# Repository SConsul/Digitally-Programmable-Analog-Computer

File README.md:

# Digitally-Programmable-Analog-Computer

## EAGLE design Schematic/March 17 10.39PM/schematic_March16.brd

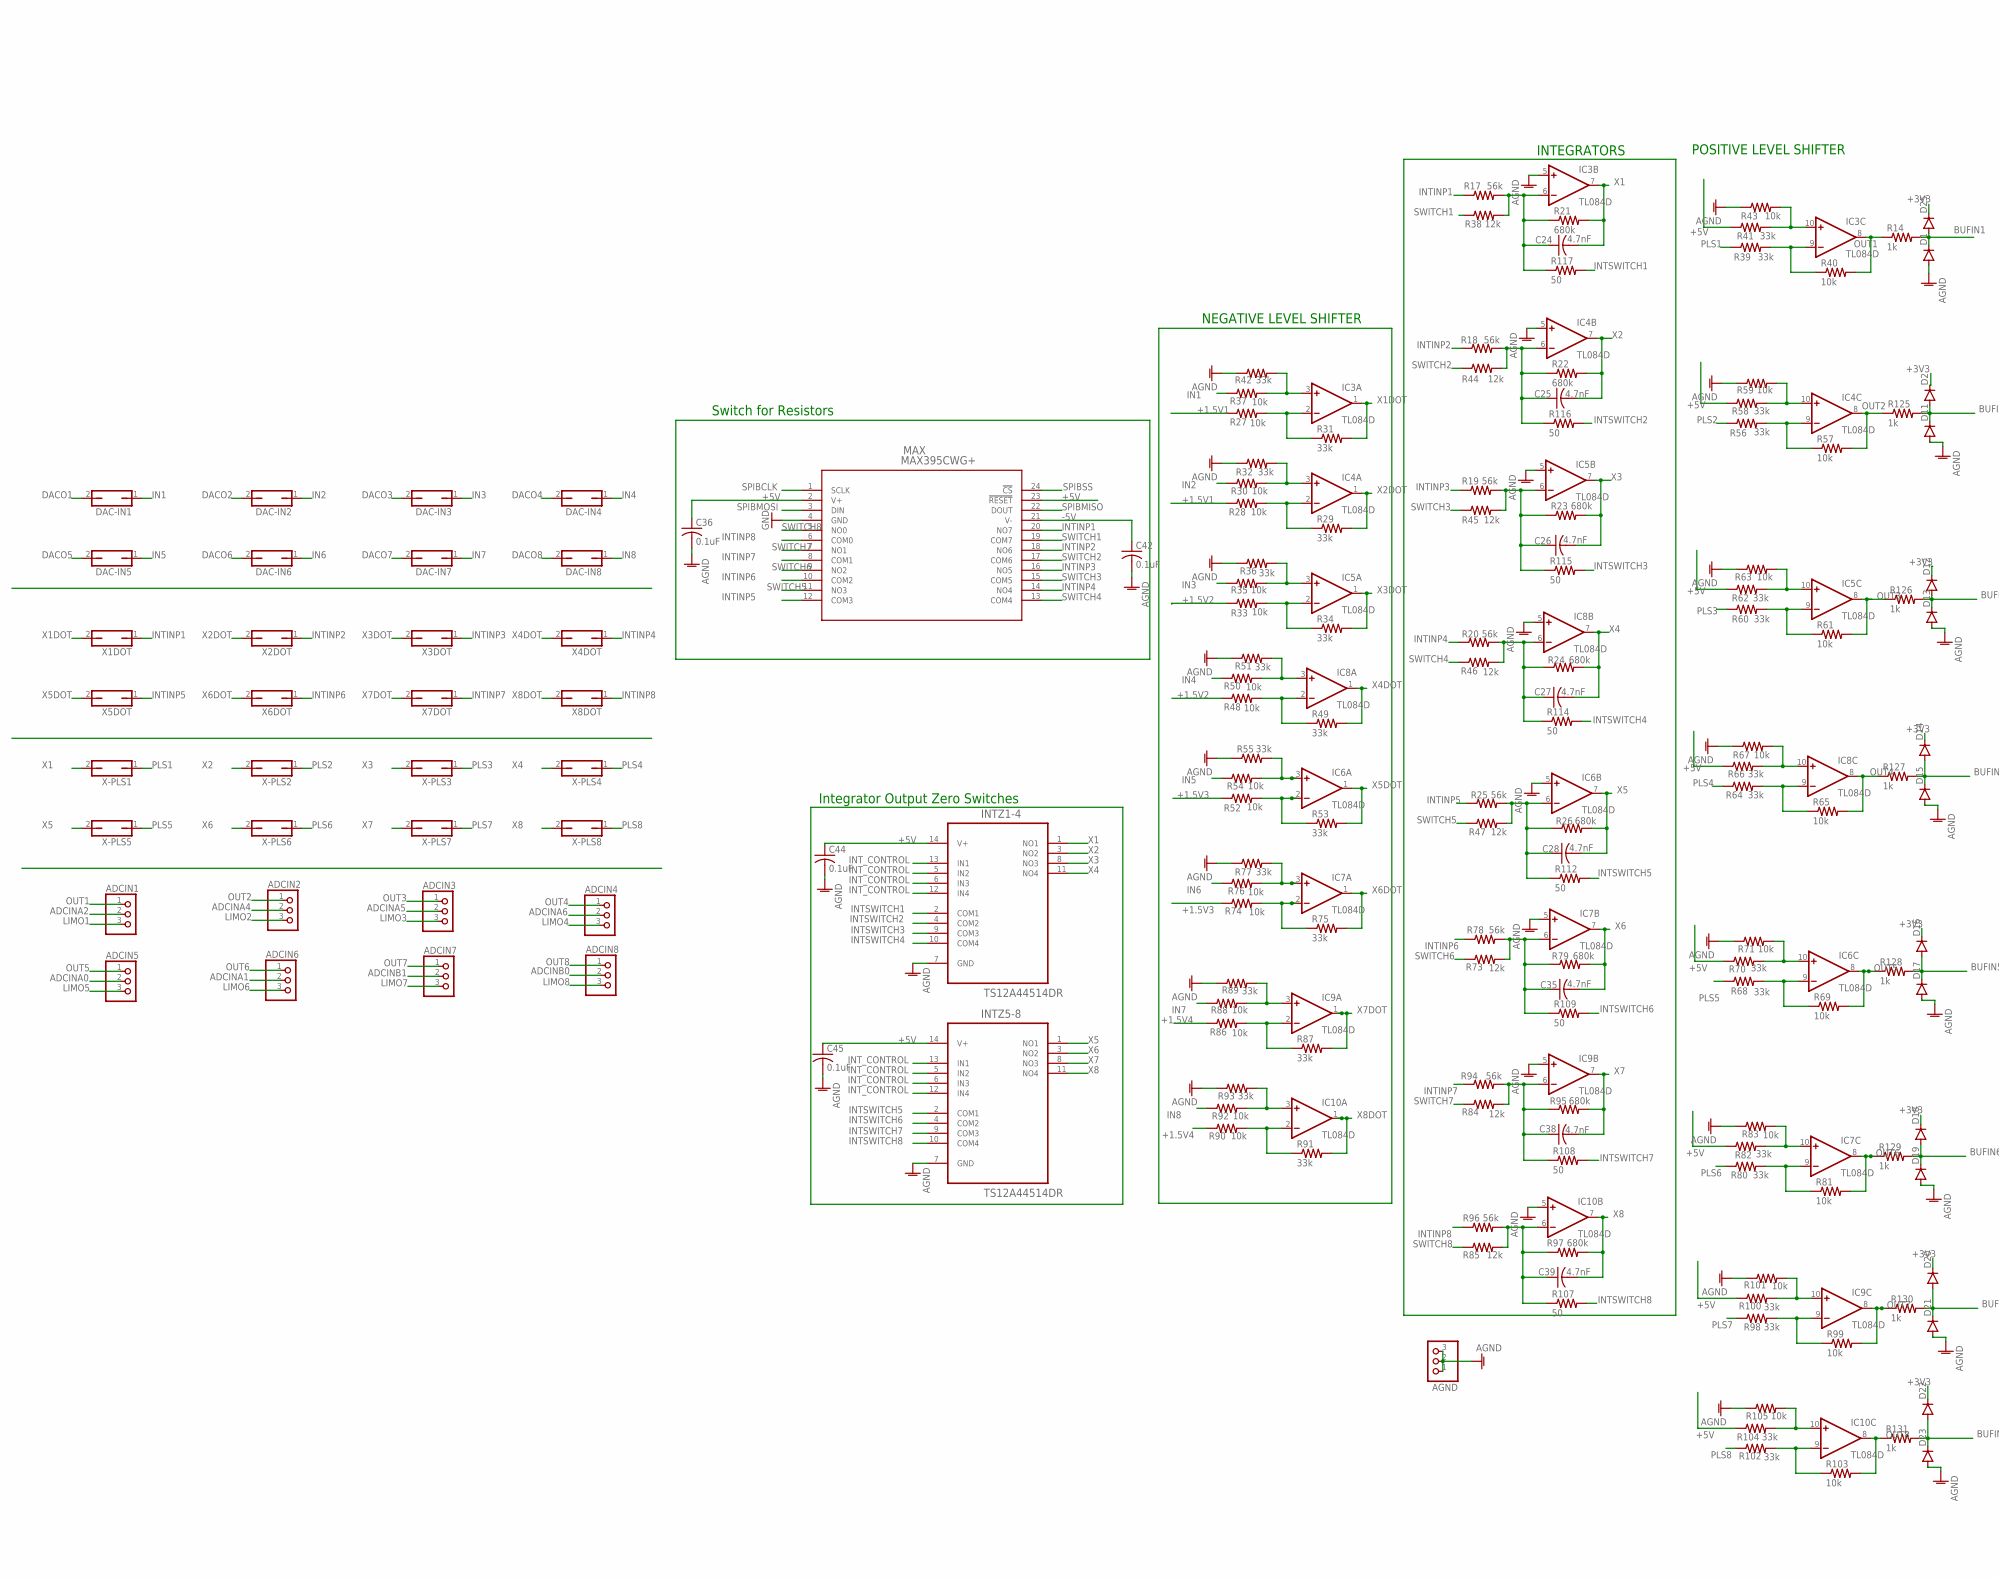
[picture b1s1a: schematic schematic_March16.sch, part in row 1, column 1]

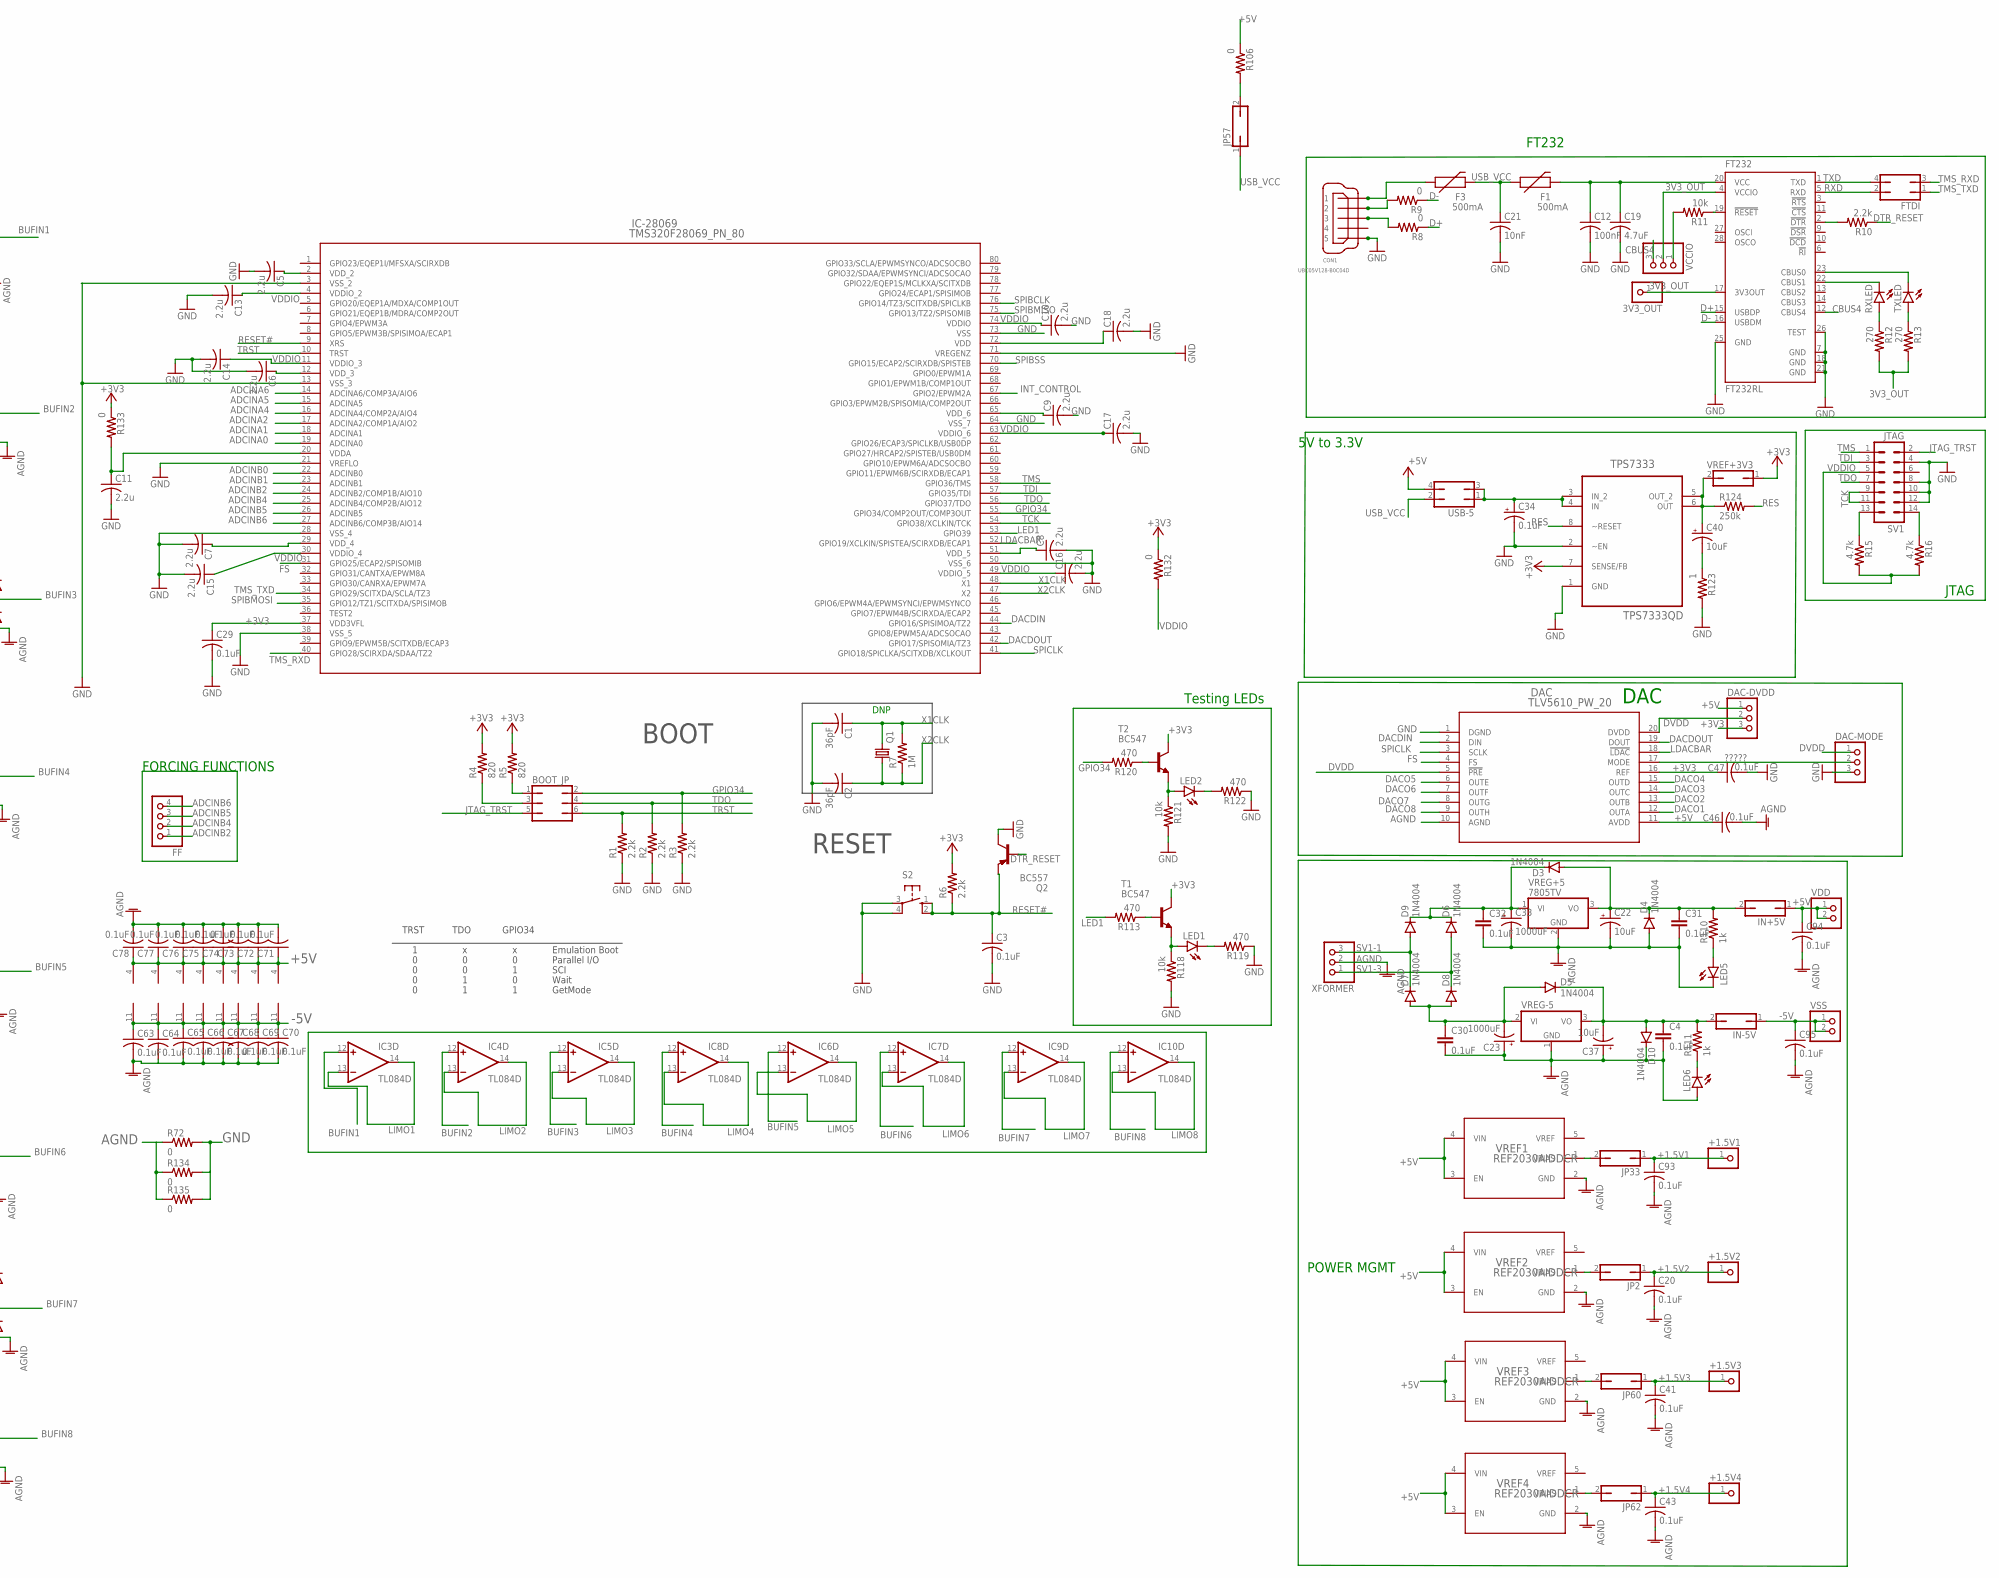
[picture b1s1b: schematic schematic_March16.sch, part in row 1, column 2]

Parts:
3V3_OUT: PINHD-1X1; 1X01
+1.5V1, +1.5V2, +1.5V3, +1.5V4: PINHD-1X1; 1X01
ADCIN1, ADCIN2, ADCIN3, ADCIN4, ADCIN5, ADCIN6, ADCIN7, ADCIN8: PINHD-1X3; 1X03
AGND: PINHD-1X3; 1X03
BOOT_JP: JP3Q
C1, C2: 36pF; C1206
C3, C4, C20, C29, C30, C31, C32, C36, C41, C42, C43, C44, C45, C46, C47, C63, C64, C65, C66, C67, C68, C69, C70, C71, C72, C73, C74, C75, C76, C77, C78, C93, C94, C95: 0.1uF; C1206
C5, C6, C7, C8, C9, C10, C11, C13, C14, C15, C16, C17, C18: 2.2u; C1206
C12: 100nF; C1206
C19: 4.7uF; C1206
C21: 10nF; C1206
C22, C37, C40: 10uF; E2,5-7
C23, C33: 1000uF; E2,5-7
C24, C25, C26, C27, C28, C35, C38, C39: 4.7nF; C1206
C34: 0.1uF; E2,5-7
CON1: UBC05V128-B0C04D; 32005-201
D1, D2, D11, D12, D13, D14, D15, D16, D17, D18, D19, D20, D21, D22, D23, D25: DIODE-DO214AA; DO214AA
D3, D4, D5, D6, D7, D8, D9, D10: 1N4004; DO41-10
DAC: TLV5610_PW_20; PW20
DAC-DVDD: PINHD-1X3; 1X03
DAC-IN1, DAC-IN2, DAC-IN3, DAC-IN4, DAC-IN5, DAC-IN6, DAC-IN7, DAC-IN8: JP1Q; JP1
DAC-MODE: PINHD-1X3; 1X03
F1, F3: 500mA; 0603
FF: PINHD-1X4; 1X04
FT232: FT232RL; SSOP28
FTDI: JP2Q
IC3, IC4, IC5, IC6, IC7, IC8, IC9, IC10: TL084D; SO14
IC-28069: TMS320F28069_PN_80; PN80
IN+5V: JP1Q; JP1
IN-5V: JP1Q; JP1
INTZ1-4, INTZ5-8: TS12A44514DR; SOIC127P600X175-14N
JP2, JP33, JP57, JP60, JP62: JP1Q; JP1
LED1, LED2, LED5, LED6: LEDSML1206; SML1206
MAX: MAX395CWG+; 21-0042B_24
Q1: CRYSTALHC49S; HC49/S
Q2: BC557; TO92-EBC
R1, R2, R3, R6, R10: 2.2k; R1206
R4, R5: 820; R1206
R7: 1M; R1206
R8, R9, R72, R106, R132, R133, R134, R135: 0; R1206
R11, R27, R28, R30, R33, R35, R37, R40, R43, R48, R50, R52, R54, R57, R59, R61, R63, R65, R67, R69, R71, R74, R76, R81, R83, R86, R88, R90, R92, R99, R101, R103, R105, R118, R121: 10k; R1206
R12, R13: 270; R1206
R14, R125, R126, R127, R128, R129, R130, R131: 1k; R1206
R15, R16: 4.7k; M1206
R17, R18, R19, R20, R25, R78, R94, R96: 56k; R1206
R21, R22, R23, R24, R26, R79, R95, R97: 680k; R1206
R29, R31, R32, R34, R36, R39, R41, R42, R49, R51, R53, R55, R56, R58, R60, R62, R64, R66, R68, R70, R75, R77, R80, R82, R87, R89, R91, R93, R98, R100, R102, R104: 33k; R1206
R38, R44, R45, R46, R47, R73, R84, R85: 12k; R1206
R107, R108, R109, R112, R114, R115, R116, R117: 50; R1206
R110, R111: 1k; 0207/10
R113, R119, R120, R122: 470; R1206
R123: 1; M1206
R124: 250k; M1206
RXLED: LEDSML1206; SML1206
S2: 10-XX; B3F-10XX
SV1: JTAG; MA07-2
T1, T2: BC547; TO92
TPS7333: TPS7333QD; SOIC127P600X175-8N
TXLED: LEDSML1206; SML1206
USB-5: JP2Q
VCCIO: PINHD-1X3; 1X03
VDD: PINHD-1X2; 1X02
VREF1, VREF2, VREF3, VREF4: REF2030AIDDCR; DDC0005A_N
VREF+3V3: JP1Q; JP1
VREG+5: 7805TV; TO220V
VREG-5: 7905T; TO220H
VSS: PINHD-1X2; 1X02
X1DOT, X2DOT, X3DOT, X4DOT, X5DOT, X6DOT, X7DOT, X8DOT: JP1Q; JP1
X-PLS1, X-PLS2, X-PLS3, X-PLS4, X-PLS5, X-PLS6, X-PLS7, X-PLS8: JP1Q; JP1
XFORMER: PINHD-1X3; 1X03

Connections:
3V3_OUT: 3V3_OUT.1, FT232.4 (VCCIO), FT232.17 (3V3OUT), R12.2, R13.2, VCCIO.2
+1.5V1: +1.5V1.1, C93.1, JP33.1, R27.1, R28.1
+1.5V2: +1.5V2.1, C20.1, JP2.1, R33.1, R48.1
+1.5V3: +1.5V3.1, C41.1, JP60.1, R52.1, R74.1
+1.5V4: +1.5V4.1, C43.1, JP62.1, R86.1, R90.1
+3V3: C29.1, C47.1, D2.C, D12.C, D14.C, D16.C, D18.C, D20.C, D22.C, D25.C, DAC.16 (REF), DAC-DVDD.3, IC-28069.37 (VDD3VFL), R4.2, R5.2, R6.2, R132.1, R133.1, T1.3 (C), T2.3 (C), TPS7333.7 (SENSE/FB), VREF+3V3.1
+5V: C36.1, C44.1, C45.1, C46.1, C71.1, C72.1, C73.1, C74.1, C75.1, C76.1, C77.1, C78.1, C94.1, DAC.11 (AVDD), DAC-DVDD.1, IC3.4 (V+), IC4.4 (V+), IC5.4 (V+), IC6.4 (V+), IC7.4 (V+), IC8.4 (V+), IC9.4 (V+), IC10.4 (V+), IN+5V.1, INTZ1-4.14 (V+), INTZ5-8.14 (V+), MAX.2 (V+), MAX.23 (!RESET), R41.1, R58.1, R62.1, R66.1, R70.1, R82.1, R100.1, R104.1, R106.1, USB-5.4, VDD.1, VDD.2, VREF1.3 (EN), VREF1.4 (VIN), VREF2.3 (EN), VREF2.4 (VIN), VREF3.3 (EN), VREF3.4 (VIN), VREF4.3 (EN), VREF4.4 (VIN)
-5V: C42.1, C63.1, C64.1, C65.1, C66.1, C67.1, C68.1, C69.1, C70.1, C95.1, IC3.11 (V-), IC4.11 (V-), IC5.11 (V-), IC6.11 (V-), IC7.11 (V-), IC8.11 (V-), IC9.11 (V-), IC10.11 (V-), IN-5V.1, MAX.21 (V-), VSS.1, VSS.2
?????: DAC.17 (MODE), DAC-MODE.2
ADCINA0: ADCIN5.2, IC-28069.19 (ADCINA0)
ADCINA1: ADCIN6.2, IC-28069.18 (ADCINA1)
ADCINA2: ADCIN1.2, IC-28069.17 (ADCINA2/COMP1A/AIO2)
ADCINA4: ADCIN2.2, IC-28069.16 (ADCINA4/COMP2A/AIO4)
ADCINA5: ADCIN3.2, IC-28069.15 (ADCINA5)
ADCINA6: ADCIN4.2, IC-28069.14 (ADCINA6/COMP3A/AIO6)
ADCINB0: ADCIN8.2, IC-28069.22 (ADCINB0)
ADCINB1: ADCIN7.2, IC-28069.23 (ADCINB1)
ADCINB2: FF.1, IC-28069.24 (ADCINB2/COMP1B/AIO10)
ADCINB4: FF.2, IC-28069.25 (ADCINB4/COMP2B/AIO12)
ADCINB5: FF.3, IC-28069.26 (ADCINB5)
ADCINB6: FF.4, IC-28069.27 (ADCINB6/COMP3B/AIO14)
AGND: AGND.1, AGND.2, AGND.3, C4.2, C20.2, C22.-, C23.+, C30.2, C31.2, C32.2, C33.-, C36.2, C37.+, C41.2, C42.2, C43.2, C44.2, C45.2, C46.2, C63.2, C64.2, C65.2, C66.2, C67.2, C68.2, C69.2, C70.2, C71.2, C72.2, C73.2, C74.2, C75.2, C76.2, C77.2, C78.2, C93.2, C94.2, C95.2, D1.A, D4.A, D10.C, D11.A, D13.A, D15.A, D17.A, D19.A, D21.A, D23.A, DAC.10 (AGND), IC3.5 (+IN), IC4.5 (+IN), IC5.5 (+IN), IC6.5 (+IN), IC7.5 (+IN), IC8.5 (+IN), IC9.5 (+IN), IC10.5 (+IN), INTZ1-4.7 (GND), INTZ5-8.7 (GND), LED5.C, LED6.A, R32.1, R36.1, R42.1, R43.1, R51.1, R55.1, R59.1, R63.1, R67.1, R71.1, R72.1, R77.1, R83.1, R89.1, R93.1, R101.1, R105.1, R134.1, R135.1, VREF1.2 (GND), VREF2.2 (GND), VREF3.2 (GND), VREF4.2 (GND), VREG+5.2 (GND), VREG-5.1 (GND), XFORMER.2
BUFIN1: D1.C, D25.A, IC3.12 (+IN), R14.2
BUFIN2: D2.A, D11.C, IC4.12 (+IN), R125.2
BUFIN3: D12.A, D13.C, IC5.12 (+IN), R126.2
BUFIN4: D14.A, D15.C, IC8.12 (+IN), R127.2
BUFIN5: D16.A, D17.C, IC6.12 (+IN), R128.2
BUFIN6: D18.A, D19.C, IC7.12 (+IN), R129.2
BUFIN7: D20.A, D21.C, IC9.12 (+IN), R130.2
BUFIN8: D22.A, D23.C, IC10.12 (+IN), R131.2
CBUS4: FT232.12 (CBUS4), VCCIO.3
D+: FT232.15 (USBDP), R8.1
D-: FT232.16 (USBDM), R9.1
DACDIN: DAC.2 (DIN), IC-28069.44 (GPIO16/SPISIMOA/TZ2)
DACDOUT: DAC.19 (DOUT), IC-28069.42 (GPIO17/SPISOMIA/TZ3)
DACO1: DAC.12 (OUTA), DAC-IN1.2
DACO2: DAC.13 (OUTB), DAC-IN2.2
DACO3: DAC.14 (OUTC), DAC-IN3.2
DACO4: DAC.15 (OUTD), DAC-IN4.2
DACO5: DAC.6 (OUTE), DAC-IN5.2
DACO6: DAC.7 (OUTF), DAC-IN6.2
DACO7: DAC.8 (OUTG), DAC-IN7.2
DACO8: DAC.9 (OUTH), DAC-IN8.2
DTR_RESET: Q2.B, R10.1
DVDD: DAC.5 (!PRE), DAC.20 (DVDD), DAC-DVDD.2, DAC-MODE.1
FS: DAC.4 (FS), IC-28069.31 (GPIO25/ECAP2/SPISOMIB)
GND: C1.2, C2.2, C3.2, C5.2, C6.2, C7.2, C8.2, C9.2, C10.2, C11.2, C12.2, C13.2, C14.2, C15.2, C16.2, C17.2, C18.2, C19.2, C21.2, C29.2, C34.-, C47.2, CON1.5, DAC.1 (DGND), DAC-MODE.3, FT232.7 (GND), FT232.18 (GND), FT232.21 (GND), FT232.25 (GND), FT232.26 (TEST), IC-28069.3 (VSS_2), IC-28069.13 (VSS_3), IC-28069.21 (VREFLO), IC-28069.28 (VSS_4), IC-28069.38 (VSS_5), IC-28069.50 (VSS_6), IC-28069.64 (VSS_7), IC-28069.71 (VREGENZ), IC-28069.73 (VSS), MAX.4 (GND), Q2.C, R1.1, R2.1, R3.1, R72.2, R118.2, R119.1, R121.2, R122.1, R123.2, R134.2, R135.2, S2.3, S2.4 (P1), SV1.4, SV1.8, SV1.10, SV1.12, TPS7333.1 (GND), TPS7333.2 (~EN)
GPIO34: BOOT_JP.2, IC-28069.55 (GPIO34/COMP2OUT/COMP3OUT), R3.2, R120.2
IDK: C22.+, C31.1, D3.A, D4.C, IN+5V.2, R110.2, VREG+5.3 (VO)
IDK2: C4.1, C37.-, D5.C, D10.A, IN-5V.2, R111.2, VREG-5.3 (VO)
IN1: DAC-IN1.1, R37.1
IN2: DAC-IN2.1, R30.1
IN3: DAC-IN3.1, R35.1
IN4: DAC-IN4.1, R50.1
IN5: DAC-IN5.1, R54.1
IN6: DAC-IN6.1, R76.1
IN7: DAC-IN7.1, R88.1
IN8: DAC-IN8.1, R92.1
INTINP1: MAX.20 (NO7), R17.1, X1DOT.1
INTINP2: MAX.18 (NO6), R18.1, X2DOT.1
INTINP3: MAX.16 (NO5), R19.1, X3DOT.1
INTINP4: MAX.14 (NO4), R20.1, X4DOT.1
INTINP5: MAX.12 (COM3), R25.1, X5DOT.1
INTINP6: MAX.10 (COM2), R78.1, X6DOT.1
INTINP7: MAX.8 (COM1), R94.1, X7DOT.1
INTINP8: MAX.6 (COM0), R96.1, X8DOT.1
INTSWITCH1: INTZ1-4.2 (COM1), R117.2
INTSWITCH2: INTZ1-4.4 (COM2), R116.2
INTSWITCH3: INTZ1-4.9 (COM3), R115.2
INTSWITCH4: INTZ1-4.10 (COM4), R114.2
INTSWITCH5: INTZ5-8.2 (COM1), R112.2
INTSWITCH6: INTZ5-8.4 (COM2), R109.2
INTSWITCH7: INTZ5-8.9 (COM3), R108.2
INTSWITCH8: INTZ5-8.10 (COM4), R107.2
INT_CONTROL: IC-28069.67 (GPIO2/EPWM2A), INTZ1-4.5 (IN2), INTZ1-4.6 (IN3), INTZ1-4.12 (IN4), INTZ1-4.13 (IN1), INTZ5-8.5 (IN2), INTZ5-8.6 (IN3), INTZ5-8.12 (IN4), INTZ5-8.13 (IN1)
JTAG_TRST: BOOT_JP.5, SV1.2
LDACBAR: DAC.18 (!LDAC), IC-28069.52 (GPIO19/XCLKIN/SPISTEA/SCIRXDB/ECAP1)
LED1: IC-28069.53 (GPIO39), R113.2
LIMO1: ADCIN1.3, IC3.13 (-IN), IC3.14 (OUT)
LIMO2: ADCIN2.3, IC4.13 (-IN), IC4.14 (OUT)
LIMO3: ADCIN3.3, IC5.13 (-IN), IC5.14 (OUT)
LIMO4: ADCIN4.3, IC8.13 (-IN), IC8.14 (OUT)
LIMO5: ADCIN5.3, IC6.13 (-IN), IC6.14 (OUT)
LIMO6: ADCIN6.3, IC7.13 (-IN), IC7.14 (OUT)
LIMO7: ADCIN7.3, IC9.13 (-IN), IC9.14 (OUT)
LIMO8: ADCIN8.3, IC10.13 (-IN), IC10.14 (OUT)
unnamed: C5.1, IC-28069.2 (VDD_2)
unnamed: C6.1, IC-28069.12 (VDD_3)
unnamed: C7.1, IC-28069.29 (VDD_4)
unnamed: C8.1, IC-28069.51 (VDD_5)
unnamed: C9.1, IC-28069.65 (VDD_6)
unnamed: FT232.2 (!DTR), R10.2
unnamed: C11.1, IC-28069.20 (VDDA), R133.2
unnamed: C18.1, IC-28069.72 (VDD)
unnamed: BOOT_JP.1, R5.1
unnamed: BOOT_JP.3, R4.1
unnamed: CON1.2, R9.2
unnamed: CON1.3, R8.2
unnamed: FT232.19 (!RESET), R11.1
unnamed: FT232.22 (CBUS1), RXLED.C
unnamed: FT232.23 (CBUS0), TXLED.C
unnamed: R12.1, RXLED.A
unnamed: R13.1, TXLED.A
unnamed: C25.1, IC4.6 (-IN), R18.2, R22.1, R44.2, R116.1
unnamed: C26.1, IC5.6 (-IN), R19.2, R23.1, R45.2, R115.1
unnamed: C27.1, IC8.6 (-IN), R20.2, R24.1, R46.2, R114.1
unnamed: IC4.2 (-IN), R28.2, R29.1
unnamed: R15.1, SV1.13
unnamed: R16.1, SV1.14
unnamed: IC4.3 (+IN), R30.2, R32.2
unnamed: C24.1, IC3.6 (-IN), R17.2, R21.1, R38.2, R117.1
unnamed: IC3.2 (-IN), R27.2, R31.1
unnamed: C28.1, IC6.6 (-IN), R25.2, R26.1, R47.2, R112.1
unnamed: IC5.2 (-IN), R33.2, R34.1
unnamed: IC3.3 (+IN), R37.2, R42.2
unnamed: IC5.3 (+IN), R35.2, R36.2
unnamed: IC3.9 (-IN), R39.2, R40.1
unnamed: IC3.10 (+IN), R41.2, R43.2
unnamed: IC8.2 (-IN), R48.2, R49.1
unnamed: IC8.3 (+IN), R50.2, R51.2
unnamed: IC7.2 (-IN), R74.2, R75.1
unnamed: IC6.2 (-IN), R52.2, R53.1
unnamed: IC6.3 (+IN), R54.2, R55.2
unnamed: IC7.3 (+IN), R76.2, R77.2
unnamed: IC4.9 (-IN), R56.2, R57.1
unnamed: IC4.10 (+IN), R58.2, R59.2
unnamed: IC5.9 (-IN), R60.2, R61.1
unnamed: IC5.10 (+IN), R62.2, R63.2
unnamed: IC8.9 (-IN), R64.2, R65.1
unnamed: IC8.10 (+IN), R66.2, R67.2
unnamed: IC6.9 (-IN), R68.2, R69.1
unnamed: IC6.10 (+IN), R70.2, R71.2
unnamed: C35.1, IC7.6 (-IN), R73.2, R78.2, R79.1, R109.1
unnamed: IC7.9 (-IN), R80.2, R81.1
unnamed: IC7.10 (+IN), R82.2, R83.2
unnamed: IC9.2 (-IN), R86.2, R87.1
unnamed: IC9.3 (+IN), R88.2, R89.2
unnamed: IC10.2 (-IN), R90.2, R91.1
unnamed: IC10.3 (+IN), R92.2, R93.2
unnamed: C38.1, IC9.6 (-IN), R84.2, R94.2, R95.1, R108.1
unnamed: C39.1, IC10.6 (-IN), R85.2, R96.2, R97.1, R107.1
unnamed: IC9.9 (-IN), R98.2, R99.1
unnamed: IC9.10 (+IN), R100.2, R101.2
unnamed: IC10.9 (-IN), R102.2, R103.1
unnamed: IC10.10 (+IN), R104.2, R105.2
unnamed: C32.1, C33.+, D3.C, D6.C, D9.C, VREG+5.1 (VI)
unnamed: C40.+, R124.1, TPS7333.5 (OUT_2), TPS7333.6 (OUT), VREF+3V3.2
unnamed: C40.-, R123.1
unnamed: LED6.C, R111.1
unnamed: C34.+, TPS7333.3 (IN_2), TPS7333.4 (IN), USB-5.1, USB-5.3
unnamed: LED5.A, R110.1
unnamed: CON1.1, F3.1
unnamed: C23.-, C30.1, D5.A, D7.A, D8.A, VREG-5.2 (VI)
unnamed: JP33.2, VREF1.1 (VBIAS)
unnamed: R11.2, VCCIO.1
unnamed: R113.1, T1.2 (B)
unnamed: LED1.A, R118.1, T1.1 (E)
unnamed: LED1.C, R119.2
unnamed: R120.1, T2.2 (B)
unnamed: LED2.A, R121.1, T2.1 (E)
unnamed: LED2.C, R122.2
unnamed: JP2.2, VREF2.1 (VBIAS)
unnamed: JP57.2, R106.2
unnamed: JP60.2, VREF3.1 (VBIAS)
unnamed: JP62.2, VREF4.1 (VBIAS)
OUT1: ADCIN1.1, IC3.8 (OUT), R14.1, R40.2
OUT2: ADCIN2.1, IC4.8 (OUT), R57.2, R125.1
OUT3: ADCIN3.1, IC5.8 (OUT), R61.2, R126.1
OUT4: ADCIN4.1, IC8.8 (OUT), R65.2, R127.1
OUT5: ADCIN5.1, IC6.8 (OUT), R69.2, R128.1
OUT6: ADCIN6.1, IC7.8 (OUT), R81.2, R129.1
OUT7: ADCIN7.1, IC9.8 (OUT), R99.2, R130.1
OUT8: ADCIN8.1, IC10.8 (OUT), R103.2, R131.1
PLS1: R39.1, X-PLS1.1
PLS2: R56.1, X-PLS2.1
PLS3: R60.1, X-PLS3.1
PLS4: R64.1, X-PLS4.1
PLS5: R68.1, X-PLS5.1
PLS6: R80.1, X-PLS6.1
PLS7: R98.1, X-PLS7.1
PLS8: R102.1, X-PLS8.1
RES: R124.2, TPS7333.8 (~RESET)
RESET#: C3.1, IC-28069.9 (XRS), Q2.E, R6.1, S2.1 (S), S2.2 (S1)
RXD: FT232.5 (RXD), FTDI.2
SPIBCLK: IC-28069.76 (GPIO14/TZ3/SCITXDB/SPICLKB), MAX.1 (SCLK)
SPIBMISO: IC-28069.75 (GPIO13/TZ2/SPISOMIB), MAX.22 (DOUT)
SPIBMOSI: IC-28069.35 (GPIO12/TZ1/SCITXDA/SPISIMOB), MAX.3 (DIN)
SPIBSS: IC-28069.70 (GPIO15/ECAP2/SCIRXDB/SPISTEB), MAX.24 (!CS)
SPICLK: DAC.3 (SCLK), IC-28069.41 (GPIO18/SPICLKA/SCITXDB/XCLKOUT)
SV1-1: D7.C, D9.A, XFORMER.3
SV1-3: D6.A, D8.C, XFORMER.1
SWITCH1: MAX.19 (COM7), R38.1
SWITCH2: MAX.17 (COM6), R44.1
SWITCH3: MAX.15 (COM5), R45.1
SWITCH4: MAX.13 (COM4), R46.1
SWITCH5: MAX.11 (NO3), R47.1
SWITCH6: MAX.9 (NO2), R73.1
SWITCH7: MAX.7 (NO1), R84.1
SWITCH8: MAX.5 (NO0), R85.1
TCK: IC-28069.54 (GPIO38/XCLKIN/TCK), SV1.9, SV1.11
TDI: IC-28069.57 (GPIO35/TDI), SV1.3
TDO: BOOT_JP.4, IC-28069.56 (GPIO37/TDO), R2.2, SV1.7
TMS: IC-28069.58 (GPIO36/TMS), SV1.1
TMS_RXD: FTDI.3, IC-28069.40 (GPIO28/SCIRXDA/SDAA/TZ2)
TMS_TXD: FTDI.1, IC-28069.34 (GPIO29/SCITXDA/SCLA/TZ3)
TRST: BOOT_JP.6, IC-28069.10 (TRST), R1.2
TXD: FT232.1 (TXD), FTDI.4
USB_VCC: C21.1, F1.1, F3.2, JP57.1, USB-5.2
VCC: C12.1, C19.1, F1.2, FT232.20 (VCC)
VDDIO: C10.1, C13.1, C14.1, C15.1, C16.1, C17.1, IC-28069.4 (VDDIO_2), IC-28069.11 (VDDIO_3), IC-28069.30 (VDDIO_4), IC-28069.49 (VDDIO_5), IC-28069.63 (VDDIO_6), IC-28069.74 (VDDIO), R15.2, R16.2, R132.2, SV1.5
X1: C24.2, IC3.7 (OUT), INTZ1-4.1 (NO1), R21.2, X-PLS1.2
X1CLK: C1.1, IC-28069.48 (X1), Q1.2, R7.2
X1DOT: IC3.1 (OUT), R31.2, X1DOT.2
X2: C25.2, IC4.7 (OUT), INTZ1-4.3 (NO2), R22.2, X-PLS2.2
X2CLK: C2.1, IC-28069.47 (X2), Q1.1, R7.1
X2DOT: IC4.1 (OUT), R29.2, X2DOT.2
X3: C26.2, IC5.7 (OUT), INTZ1-4.8 (NO3), R23.2, X-PLS3.2
X3DOT: IC5.1 (OUT), R34.2, X3DOT.2
X4: C27.2, IC8.7 (OUT), INTZ1-4.11 (NO4), R24.2, X-PLS4.2
X4DOT: IC8.1 (OUT), R49.2, X4DOT.2
X5: C28.2, IC6.7 (OUT), INTZ5-8.1 (NO1), R26.2, X-PLS5.2
X5DOT: IC6.1 (OUT), R53.2, X5DOT.2
X6: C35.2, IC7.7 (OUT), INTZ5-8.3 (NO2), R79.2, X-PLS6.2
X6DOT: IC7.1 (OUT), R75.2, X6DOT.2
X7: C38.2, IC9.7 (OUT), INTZ5-8.8 (NO3), R95.2, X-PLS7.2
X7DOT: IC9.1 (OUT), R87.2, X7DOT.2
X8: C39.2, IC10.7 (OUT), INTZ5-8.11 (NO4), R97.2, X-PLS8.2
X8DOT: IC10.1 (OUT), R91.2, X8DOT.2

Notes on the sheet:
TDO
GPIO34
TRST
Emulation Boot
Parallel I/O
SCI
Wait
GetMode
BOOT
RESET
DNP
INTEGRATORS
NEGATIVE LEVEL SHIFTER
POSITIVE LEVEL SHIFTER
FT232
5V to 3.3V
JTAG
DAC
FORCING FUNCTIONS
POWER MGMT
Integrator Output Zero Switches
Testing LEDs
Switch for Resistors

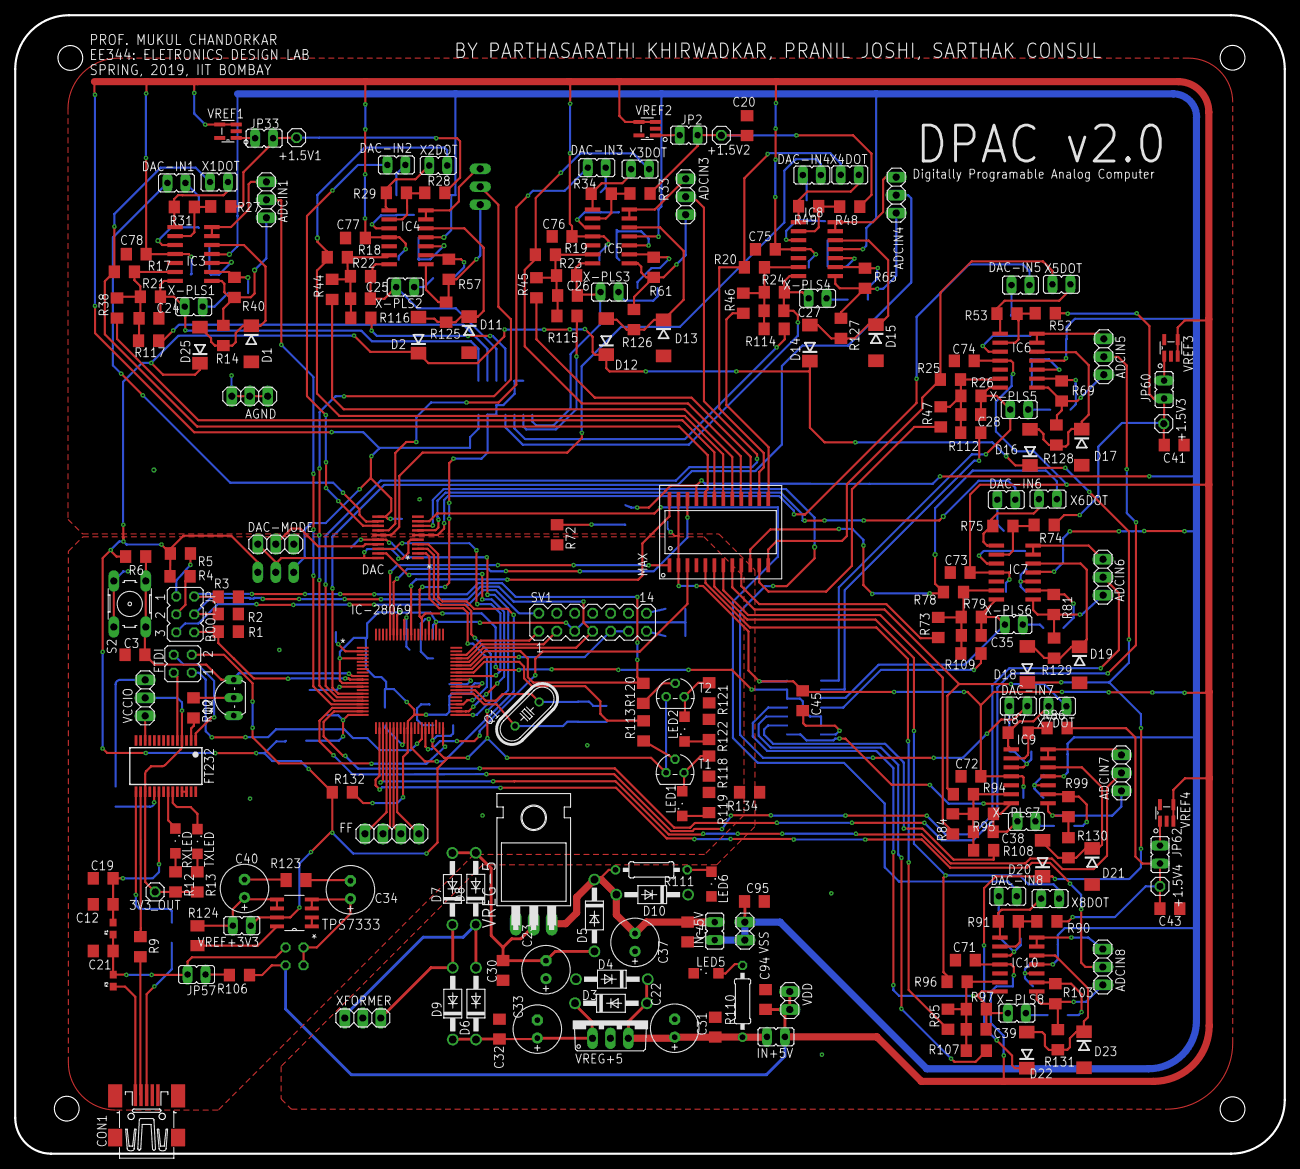
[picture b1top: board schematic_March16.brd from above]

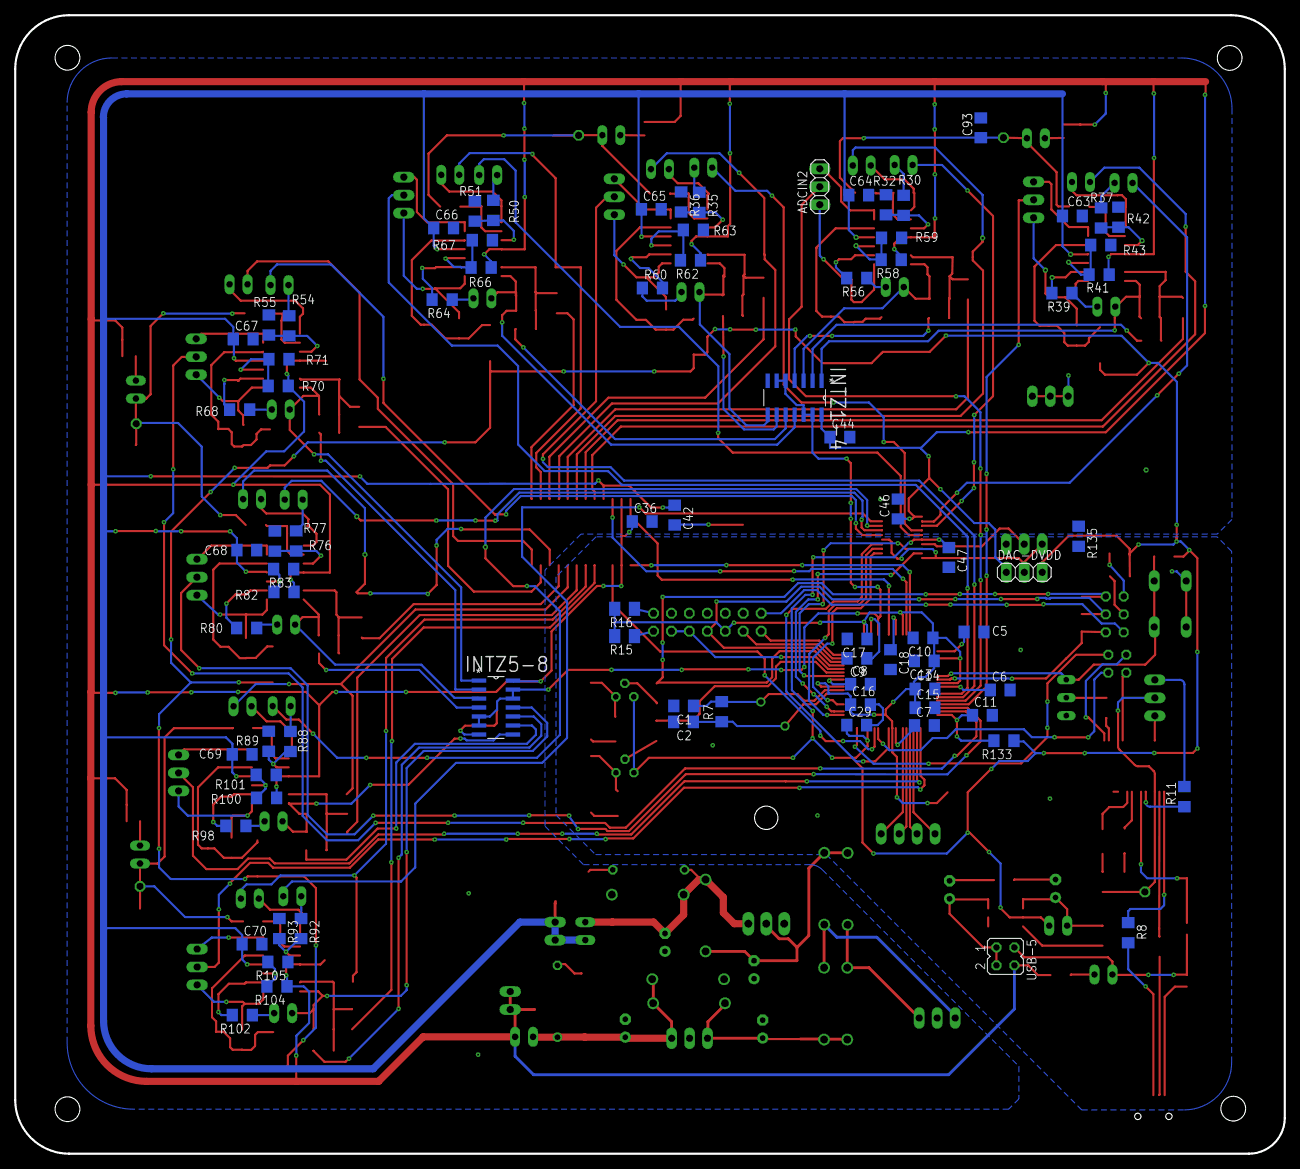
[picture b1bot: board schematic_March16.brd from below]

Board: 2 copper layers, 179.6 x 161.1 mm, 317 parts (82 on the bottom side), 228 nets.
